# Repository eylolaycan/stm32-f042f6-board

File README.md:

# stm32-f042f6-board
Hardware-only STM32F042F6 development board designed in KiCad 9.

## Prevision History
Prevision 1: Board created.

## Notes
Missing connections.

## Gallery

## License
CC0 1.0 Universal

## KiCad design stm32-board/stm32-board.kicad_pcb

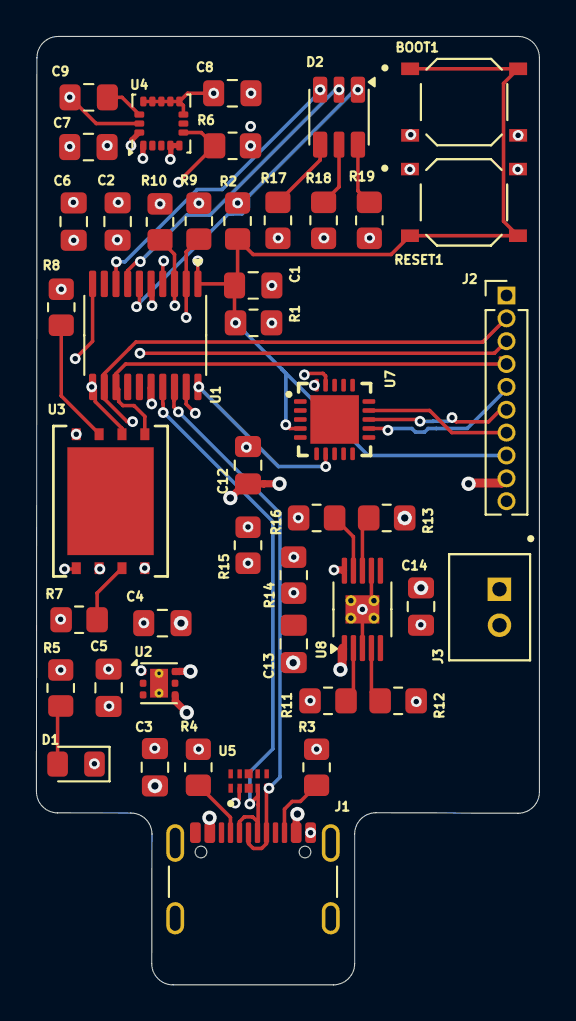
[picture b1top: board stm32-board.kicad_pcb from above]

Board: 6 copper layers, 27.9 x 52.7 mm, 45 parts (0 on the bottom side), 36 nets.

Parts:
BOOT1: PTS526; SW_PTS526_SM08_SMTR2_LFS
C1, C8, C9: 0.1uF; C_0805_2012Metric_Pad1.18x1.45mm_HandSolder
C2, C4, C5, C6, C12, C13, C14: 1uF; C_0805_2012Metric_Pad1.18x1.45mm_HandSolder
C3: 10uF; C_0805_2012Metric_Pad1.18x1.45mm_HandSolder
C7: 2.2uF; C_0805_2012Metric_Pad1.18x1.45mm_HandSolder
D1: LED; LED_0805_2012Metric_Pad1.15x1.40mm_HandSolder
D2: SMLVN6RGB; LED_ROHM_SMLVN6
J1: USB_C_Receptacle_USB2.0_16P; USB_C_Receptacle_GCT_USB4105-xx-A_16P_TopMnt_Horizontal
J2: Conn_01x10_Pin; PinHeader_1x10_P1.27mm_Vertical
J3: B2B-PH-K-S; JST_B2B-PH-K-S
R1, R2, R7, R8: 10k; R_0805_2012Metric_Pad1.20x1.40mm_HandSolder
R3, R4: 5.1K; R_0805_2012Metric_Pad1.20x1.40mm_HandSolder
R5, R11, R17, R18, R19: 1k; R_0805_2012Metric_Pad1.20x1.40mm_HandSolder
R6: 10K; R_0805_2012Metric_Pad1.20x1.40mm_HandSolder
R9, R10: 4.7k; R_0805_2012Metric_Pad1.20x1.40mm_HandSolder
R12, R13, R14, R15: 2k; R_0805_2012Metric_Pad1.20x1.40mm_HandSolder
R16: 100k; R_0805_2012Metric_Pad1.20x1.40mm_HandSolder
RESET1: PTS526; SW_PTS526_SM08_SMTR2_LFS
U1: STM32F042F6Px; TSSOP-20_4.4x6.5mm_P0.65mm
U2: LP5912-3.3DRV; WSON-6-1EP_2x2mm_P0.65mm_EP1x1.6mm_ThermalVias
U3: SST25VF020B-80-4C-QAE; WSON8_Q2A_SST_MCH-M
U4: ICM-20602; LGA-16_3x3mm_P0.5mm_LayoutBorder3x5y
U5: DIO_ESDR0524PMUTAG
U7: MCP23008-E_ML; QFN21P50_400X400X100L40X24T270N
U8: BQ24090DGQ; HVSSOP-10-1EP_3x3mm_P0.5mm_EP1.57x1.88mm_ThermalVias

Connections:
/3v3: BOOT1.3, BOOT1.4, C2.1, C5.2, C6.2, C7.1, C8.1, R2.1, R5.1, R6.1, R7.1, R8.1, R9.1, R10.1, U1.5 (VDDA), U1.16 (VDD), U2.1 (OUT), U3.8 (VDD), U4.1 (VDDIO), U4.4 (SAO/SD0), U4.5 (~CS), U4.16 (VDD)
/5vUSB: C3.1, C4.2, C12.2, C13.1, J1.A4 (VBUS), J1.A9 (VBUS), J1.B4 (VBUS), J1.B9 (VBUS), J2.9, U2.4 (EN), U2.6 (IN), U5.2 (I/O), U7.18 (VDD), U8.1 (IN)
/ACCEL_INT: R6.2, U1.19 (PA13), U4.6 (INT)
/BOOT: BOOT1.1, BOOT1.2, C1.1, J2.8, R1.1, R2.2, RESET1.3, RESET1.4, U1.1 (PB8), U1.4 (NRST), U7.4 (~RESET)
/CARD_CS: J2.6, U7.13 (GP4)
/D/C: J2.7, U7.14 (GP5)
/I2C_SCL: R10.2, U1.3 (PF1), U4.2 (SCL/SPC), U7.19 (SCL)
/I2C_SDA: R9.2, U1.2 (PF0), U4.3 (SDA/SDI), U7.20 (SDA)
/IO_INT: U1.20 (PA14), U7.7 (INT)
/LITE_PWM: J2.1, U1.14 (PB1)
/MEM_nCE: U1.10 (PA4), U3.1 (*CE)
/RGB_B: D2.1 (BA), U1.6 (PA0)
/RGB_G: D2.3 (GA), U1.8 (PA2)
/RGB_R: D2.2 (RA), U1.7 (PA1)
/SPI1_MISO: J2.2, U1.12 (PA6), U3.2 (SO)
/SPI1_MOSI: J2.4, U1.13 (PA7), U3.5 (SI)
/SPI1_SCK: J2.3, U1.11 (PA5), U3.6 (SCK)
/TFT_CS: J2.5, U7.12 (GP3)
/USB_DM: J1.A7 (D-), J1.B7 (D-), U1.17 (PA9/PA11), U5.4 (I/O)
/USB_DP: J1.A6 (D+), J1.B6 (D+), U1.18 (PA10/PA12), U5.5 (I/O)
/VBAT: C14.1, J3.1, R13.1, R14.2, U8.10 (OUT)
/VBAT_SNS: R14.1, R15.2
/nCHG: R13.2, U8.8 (~CHG)
GND: C1.2, C2.2, C3.2, C4.1, C5.1, C6.1, C7.2, C8.2, C9.2, C12.1, C13.2, C14.2, D1.1 (K), J1.A1 (GND), J1.A12 (GND), J1.B1 (GND), J1.B12 (GND), J1.S1 (SHIELD), J2.10, J3.2, R1.2, R3.2, R4.2, R11.2, R12.2, R15.1, R16.2, R17.2, R18.2, R19.2, RESET1.1, RESET1.2, U1.15 (VSSA), U2.5 (GND), U2.7 (EP), U3.4 (VSS), U4.8 (FSYNC), U4.9 (GND), U4.10 (GND), U4.11 (GND), U4.12 (GND), U4.13 (GND), U4.15 (GND), U5.3 (GND), U5.8 (GND), U7.1 (A2), U7.2 (A1), U7.3 (A0), U7.17 (VSS), U8.3 (VSS), U8.7 (ISET2), U8.11 (VSS)
unnamed: D1.2 (A), R5.2
unnamed: D2.6 (BK), R19.1
unnamed: D2.4 (GK), R17.1
unnamed: D2.5 (RK), R18.1
unnamed: J1.A5 (CC1), R4.1
unnamed: J1.B5 (CC2), R3.1
unnamed: R8.2, U3.7 (*HOLD)
unnamed: R7.2, U3.3 (*WP)
unnamed: C9.1, U4.14 (REGOUT)
unnamed: R11.1, U8.2 (ISET)
unnamed: R12.1, U8.4 (PRETERM)
unnamed: R16.1, U8.9 (TS)

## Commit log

2025-09-15 added files
2025-09-15 Create img
2025-09-15 Rename img to note
2025-09-15 added img
2025-11-08 Add CC0 1.0 Universal License
    Added the Creative Commons CC0 1.0 Universal license to the project.
2025-11-08 Change license from MIT to CC0 1.0 Universal
